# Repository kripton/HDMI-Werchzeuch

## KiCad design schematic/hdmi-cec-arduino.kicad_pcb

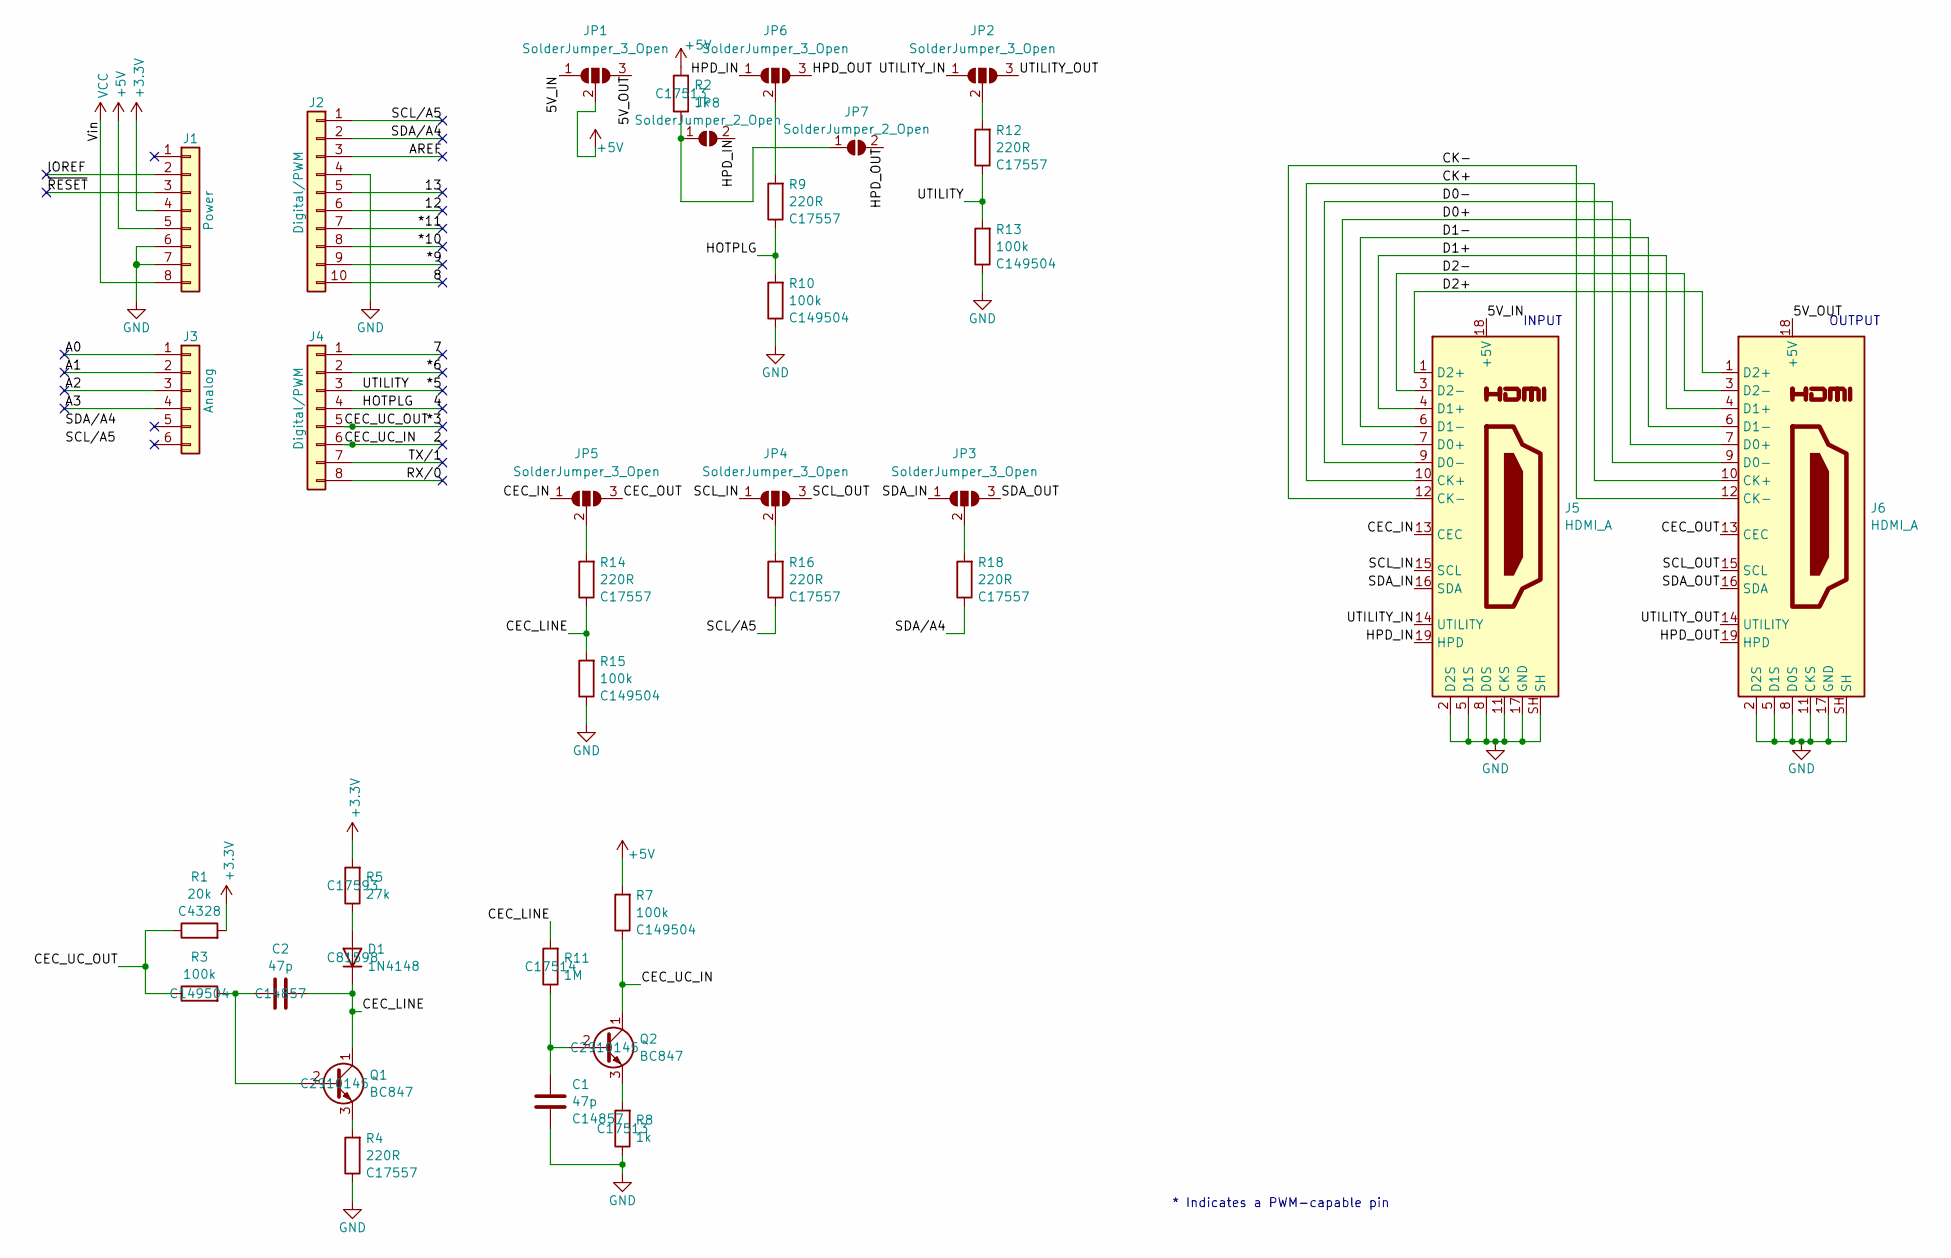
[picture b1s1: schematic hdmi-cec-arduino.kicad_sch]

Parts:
C1, C2: 47p; C_0805_2012Metric; LCSC C14857
D1: 1N4148; D_SOD-123; LCSC C81598
J1: Power; PinSocket_1x08_P2.54mm_Vertical
J2: Digital/PWM; PinSocket_1x10_P2.54mm_Vertical
J3: Analog; PinSocket_1x06_P2.54mm_Vertical
J4: Digital/PWM; PinSocket_1x08_P2.54mm_Vertical
J5, J6: HDMI_A; HDMI_A_Amphenol_10029449-x01xLF_Horizontal; LCSC C428493
JP1, JP2, JP3, JP4, JP5, JP6: SolderJumper_3_Open; SolderJumper-3_P2.0mm_Open_TrianglePad1.0x1.5mm
JP7, JP8: SolderJumper_2_Open; SolderJumper-2_P1.3mm_Open_TrianglePad1.0x1.5mm
Q1, Q2: BC847; SOT-23; LCSC C2910145
R1: 20k; R_0805_2012Metric; LCSC C4328
R2, R8: 1k; R_0805_2012Metric; LCSC C17513
R3, R7, R10, R13, R15: 100k; R_0805_2012Metric; LCSC C149504
R4, R9, R12, R14, R16, R18: 220R; R_0805_2012Metric; LCSC C17557
R5: 27k; R_0805_2012Metric; LCSC C17593
R11: 1M; R_0805_2012Metric; LCSC C17514

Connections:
+3V3: J1.4, R1.2, R5.2
+5V: J1.5, JP1.2 (C), R2.2, R7.2
/2: J4.6, Q2.1 (C), R7.1
/4: J4.4, R9.1, R10.2
/5V_IN: J5.18 (+5V), JP1.1 (A)
/5V_OUT: J6.18 (+5V), JP1.3 (B)
/7: J4.1
/8: J2.10
/12: J2.6
/13: J2.5
/*3: J4.5, R1.1, R3.1
/*5: J4.3, R12.1, R13.2
/*6: J4.2
/*9: J2.9
/*10: J2.8
/*11: J2.7
/A0: J3.1
/A1: J3.2
/A2: J3.3
/A3: J3.4
/AREF: J2.3
/CEC_IN: J5.13 (CEC), JP5.1 (A)
/CEC_LINE: C2.2, D1.1 (K), Q1.1 (C), R11.2, R14.1, R15.2
/CEC_OUT: J6.13 (CEC), JP5.3 (B)
/CK+: J5.10 (CK+), J6.10 (CK+)
/CK-: J5.12 (CK-), J6.12 (CK-)
/D0+: J5.7 (D0+), J6.7 (D0+)
/D0-: J5.9 (D0-), J6.9 (D0-)
/D1+: J5.4 (D1+), J6.4 (D1+)
/D1-: J5.6 (D1-), J6.6 (D1-)
/D2+: J5.1 (D2+), J6.1 (D2+)
/D2-: J5.3 (D2-), J6.3 (D2-)
/HPD_IN: J5.19 (HPD), JP6.1 (A), JP8.2 (B)
/HPD_OUT: J6.19 (HPD), JP6.3 (B), JP7.2 (B)
/IOREF: J1.2
/RX/0: J4.8
/SCL_IN: J5.15 (SCL), JP4.1 (A)
/SCL_OUT: J6.15 (SCL), JP4.3 (B)
/SCL/A5: J2.1, R16.1
/SDA_IN: J5.16 (SDA), JP3.1 (A)
/SDA_OUT: J6.16 (SDA), JP3.3 (B)
/SDA/A4: J2.2, R18.1
/TX/1: J4.7
/UTILITY_IN: J5.14 (UTILITY), JP2.1 (A)
/UTILITY_OUT: J6.14 (UTILITY), JP2.3 (B)
/~RESET: J1.3
GND: C1.1, J1.6, J1.7, J2.4, J5.2 (D2S), J5.5 (D1S), J5.8 (D0S), J5.11 (CKS), J5.17 (GND), J5.SH, J6.2 (D2S), J6.5 (D1S), J6.8 (D0S), J6.11 (CKS), J6.17 (GND), J6.SH, R4.1, R8.1, R10.1, R13.1, R15.1
unnamed: D1.2 (A), R5.1
unnamed: JP2.2 (C), R12.2
unnamed: JP3.2 (C), R18.2
unnamed: JP4.2 (C), R16.2
unnamed: JP5.2 (C), R14.2
unnamed: JP6.2 (C), R9.2
unnamed: JP7.1 (A), JP8.1 (A), R2.1
unnamed: C2.1, Q1.2 (B), R3.2
unnamed: Q1.3 (E), R4.2
unnamed: C1.2, Q2.2 (B), R11.1
unnamed: Q2.3 (E), R8.2
VCC: J1.8

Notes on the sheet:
OUTPUT
* Indicates a PWM-capable pin
INPUT

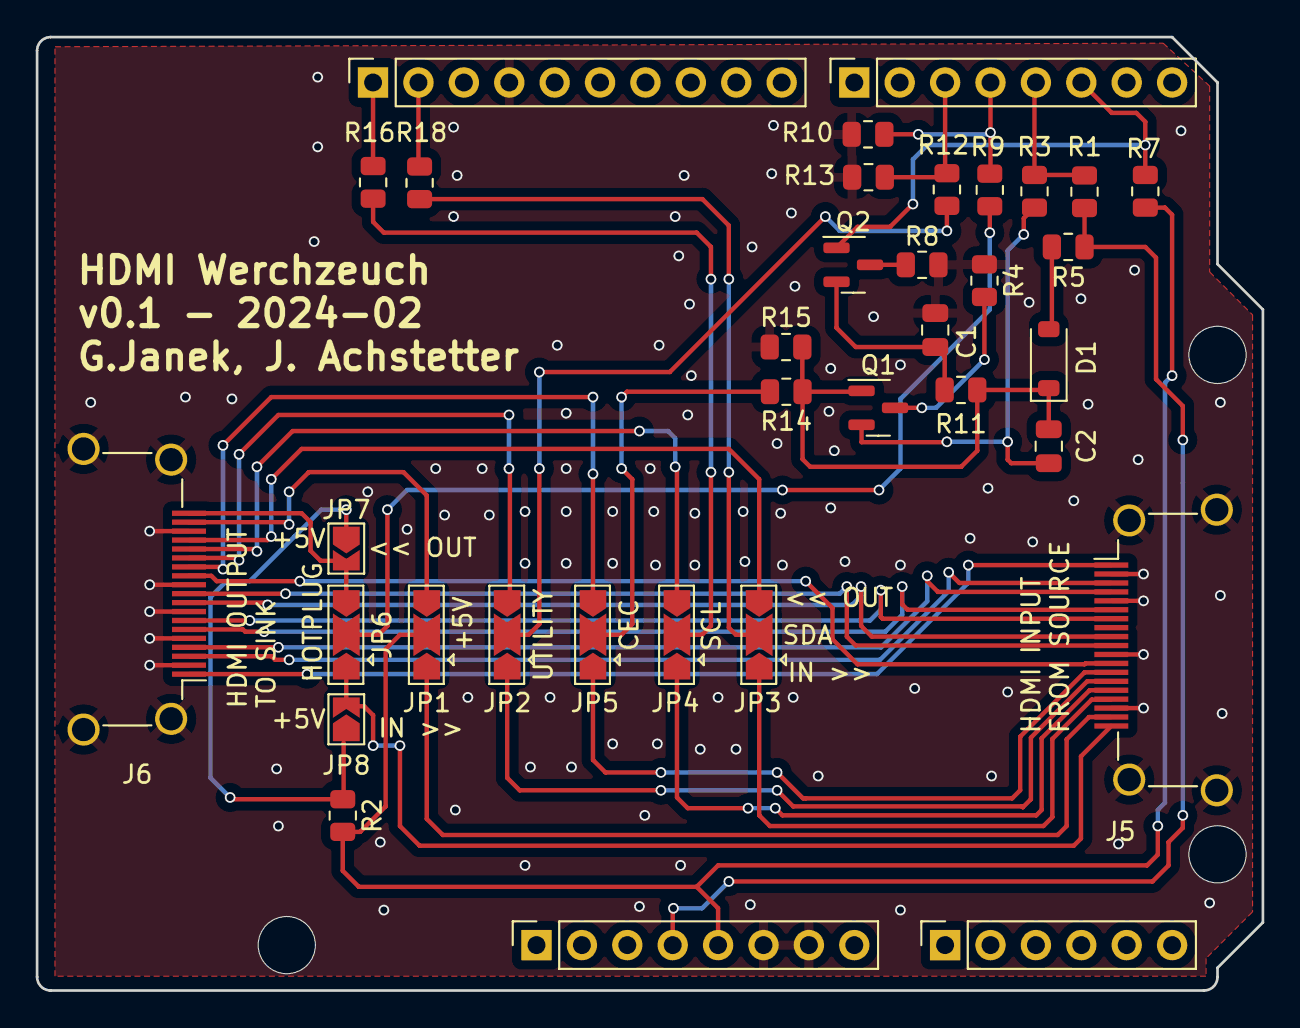
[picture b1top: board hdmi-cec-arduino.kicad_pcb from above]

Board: 2 copper layers, 68.6 x 53.3 mm, 38 parts (0 on the bottom side), 41 nets.

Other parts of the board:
MH2, MH3, MH4: MountingHole_3.2mm

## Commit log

2024-02-07 Add gitignore
2024-02-07 Add initial schematic and board
2024-02-08 Ready for production with Molex HDMI
2024-02-08 Re-Place HDMI connectors and add solder jumper for some signals
